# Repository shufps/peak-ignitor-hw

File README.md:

> 🚧 **Work in Progress**  
> This project is under active development.

# 🔥 Peak Ignitor

**Peak Ignitor** is a compact, battery-powered **high-power 12 V supply** designed for one very specific real-world problem:

> *Reliable power in cold, wind, and harsh environments.*

The original trigger was simple:  
lighting a cigarette on a mountain at –10 °C and strong wind — where gas, electric, and plasma lighters all failed.

What *did* work was a classic **car cigarette lighter**:  
wind-proof, temperature-independent, and brutally simple — as long as you can supply enough current.

That requirement immediately defines the problem space:

- 6–10 A at 12 V  
- ~120 W continuous power  
- short but demanding duty cycles  

Peak Ignitor is the result.

---

## What It Is

Peak Ignitor is a **hand-sized, self-contained 12 V power unit** capable of delivering **120 W continuously** (up to ~160 W peak), powered by a **4S Li-Ion battery pack** and designed with **thermal and mechanical constraints as first-class design inputs**.

This is not a power bank and not a jump starter — it sits deliberately in between.

---

## Key Characteristics

- 🔋 **4S Li-Ion Battery System**
  - 4S1P Samsung 18650 (30Q)
  - ~44 Wh energy
  - Proper BMS with balancing and protection
  - Battery operated close to practical limits — intentionally and transparently

- ⚡ **Regulated 12 V Output**
  - High-power buck/boost converter (TI LM51770)
  - ~120 W continuous output
  - ~160 W peak, time-limited
  - Standard automotive cigarette lighter socket

- 🧊 **Mechanics-First Thermal Design**
  - Custom-machined **solid copper heatsink**
  - Direct thermal coupling into the aluminum enclosure
  - The enclosure itself acts as a secondary heatsink
  - Temperature measurement placed directly beneath the heatsink (TMP1075)

- 🧠 **Embedded Control & Monitoring**
  - ESP32-S3 Mini-1
  - Real-time monitoring of voltage, current, power, and temperature
  - Software-enforced safety limits (not just hardware ceilings)
  - Wi-Fi Web UI for observability (because why not 😎)

- 🔌 **Integrated Charging**
  - Onboard Li-Ion charging circuit
  - Balancer connector
  - Fully self-contained — no external hobby charger required

---

## Design Approach

A central idea behind Peak Ignitor is **mechanics-first design**:

The complete 3D model — enclosure, PCB outline, mounting points, heatsink geometry, connector placement, and thermal paths — was created **before** PCB layout and component selection.

This tightly couples:

- Mechanical design  
- PCB layout and form factor  
- Thermal constraints  
- User interaction and front-panel layout  

into a single coherent system.

As a result, the PCB, heatsink, battery pack, and enclosure are not independent parts — they are **co-designed elements of one integrated structure**.

---

## Thermal Philosophy

Thermal management is not an accessory here.

Heat is transferred:
1. from the power electronics  
2. into a custom copper heatsink  
3. directly into the aluminum enclosure  

This effectively turns the entire case into an active thermal component — a design style commonly found in industrial or automotive hardware, but rarely in DIY projects.

Sustained output is **intentionally limited by battery temperature**, not by electronic capability.

---

## Typical Use Cases

- 🔥 **Car cigarette lighter**  
  6–10 A for seconds — trivial load.

- 🏄 **SUP pumps / small compressors**  
  ~110 W continuous at 12 V.

- ⛏️ **NerdQAxe++**  
  ~80 W mobile operation.

- 🔌 **General 12 V loads**  
  Measurement equipment, adapters, field hardware.

---

## What This Project Demonstrates

Peak Ignitor is less about lighting a cigarette — and more about showing what happens when:

- real-world requirements  
- harsh environmental constraints  
- and a refusal to accept “almost good enough”  

meet a **system-level engineering mindset**.

It combines:
- energy storage  
- power electronics  
- thermal engineering  
- mechanical design  
- embedded firmware  

into a compact, honest, high-power device.

---

## Notes

- High-current device — **not a toy**
- Use only suitable loads
- Do not bypass or modify protection mechanisms
- Never operate the battery without the BMS

---

> *A good horse jumps only as high as it needs to.*  
> **Peak Ignitor jumps higher — on purpose.**

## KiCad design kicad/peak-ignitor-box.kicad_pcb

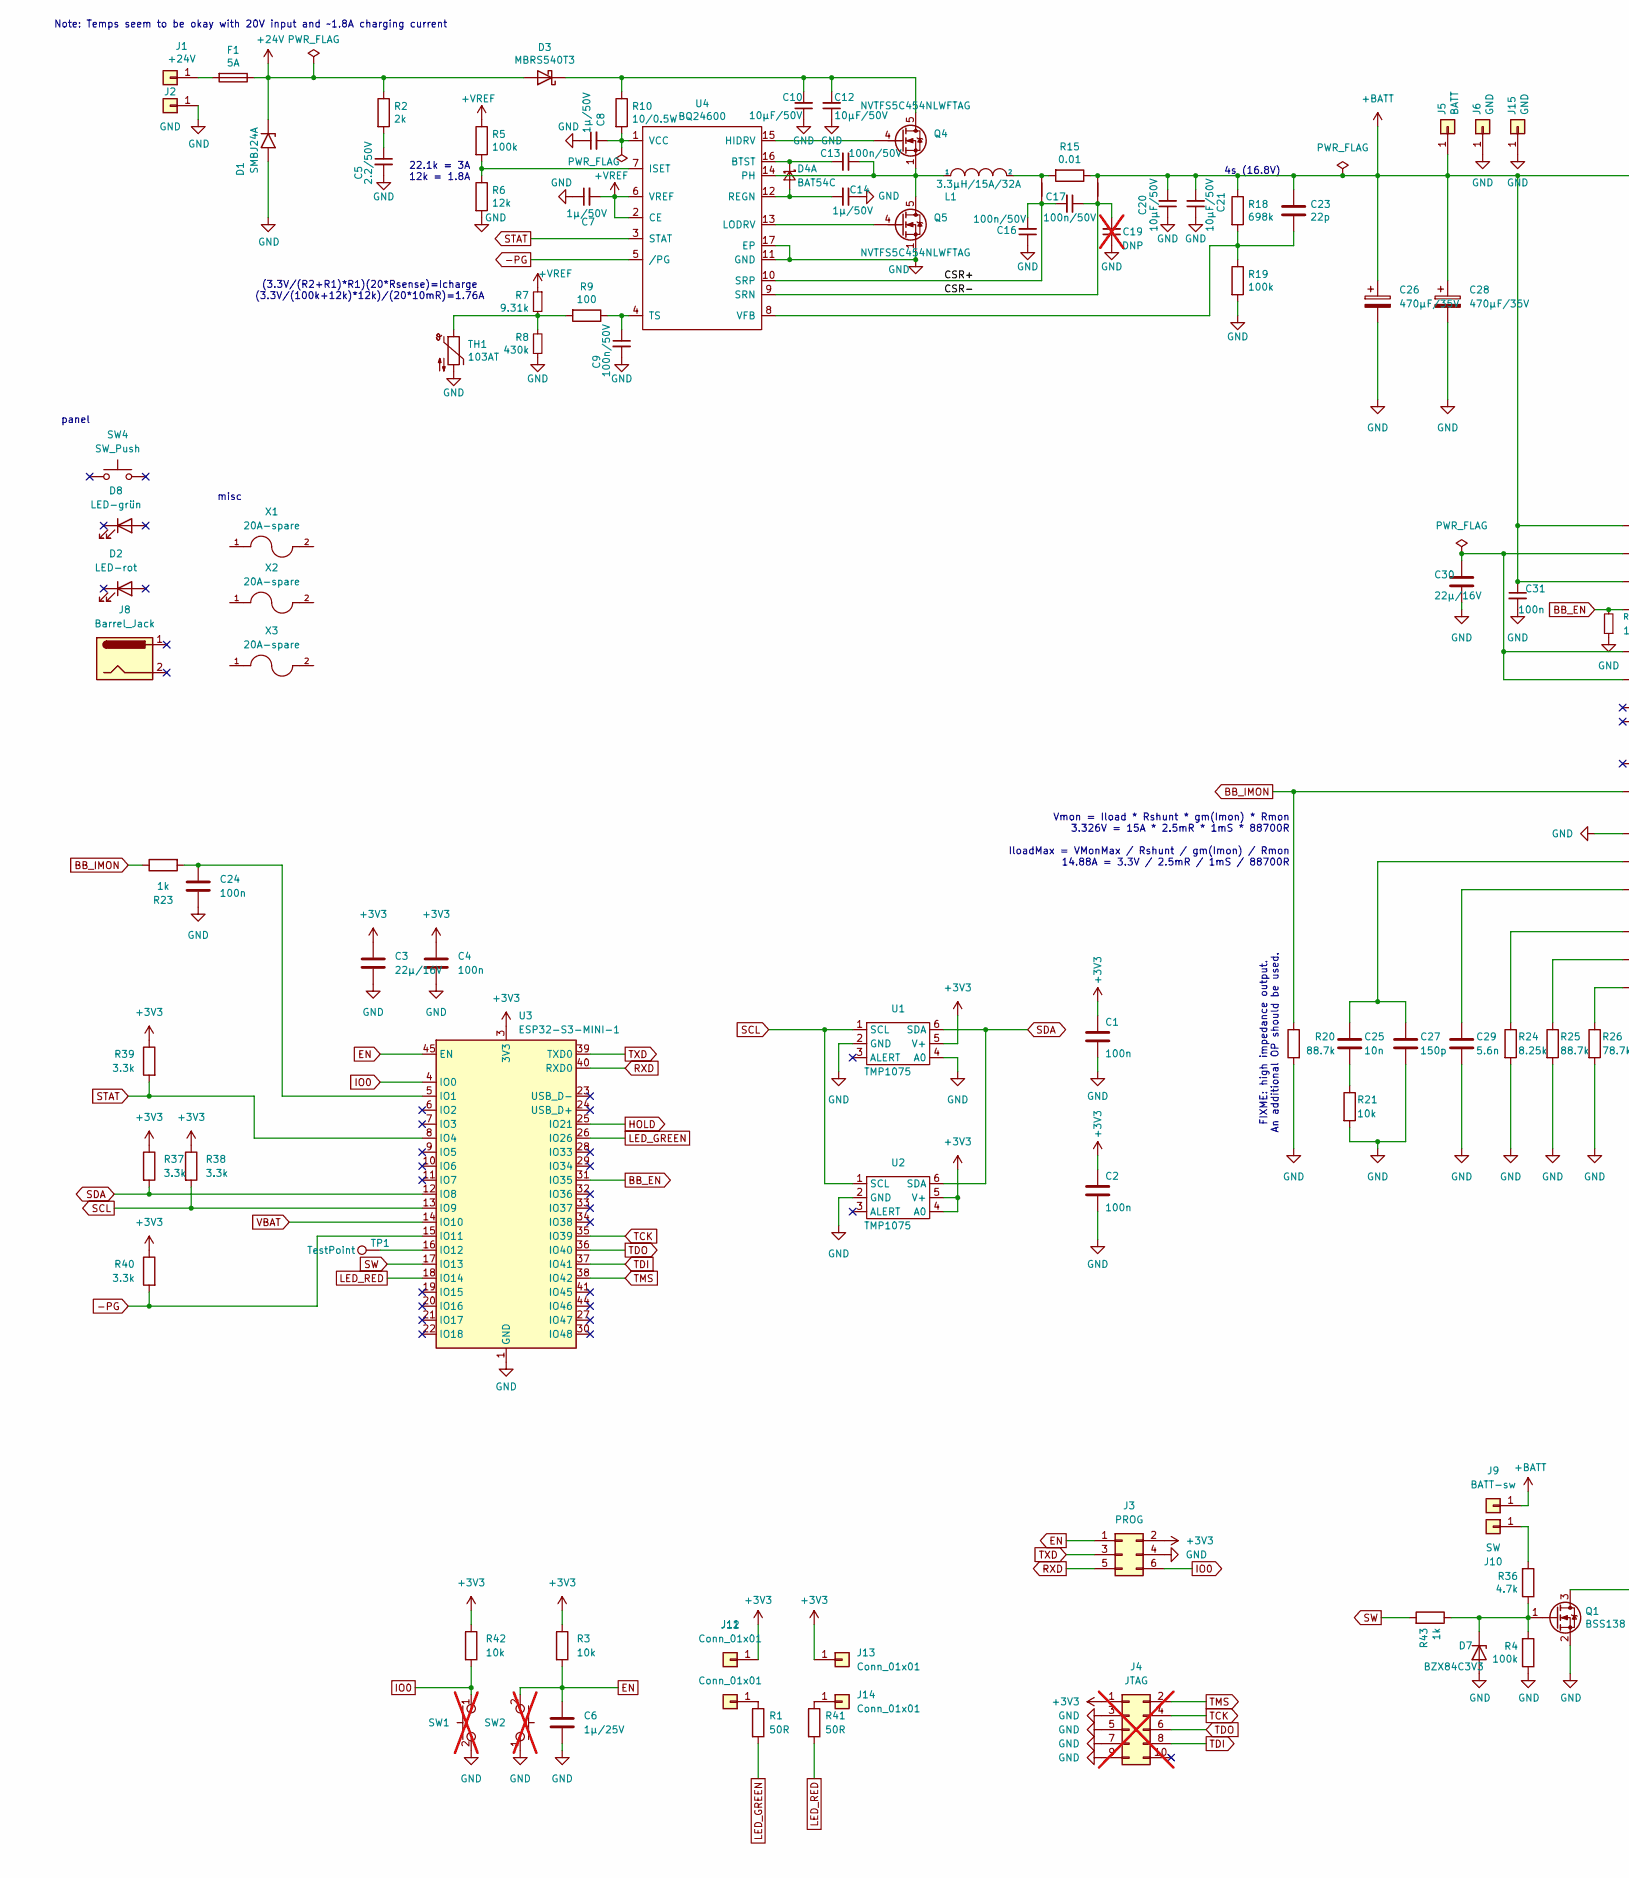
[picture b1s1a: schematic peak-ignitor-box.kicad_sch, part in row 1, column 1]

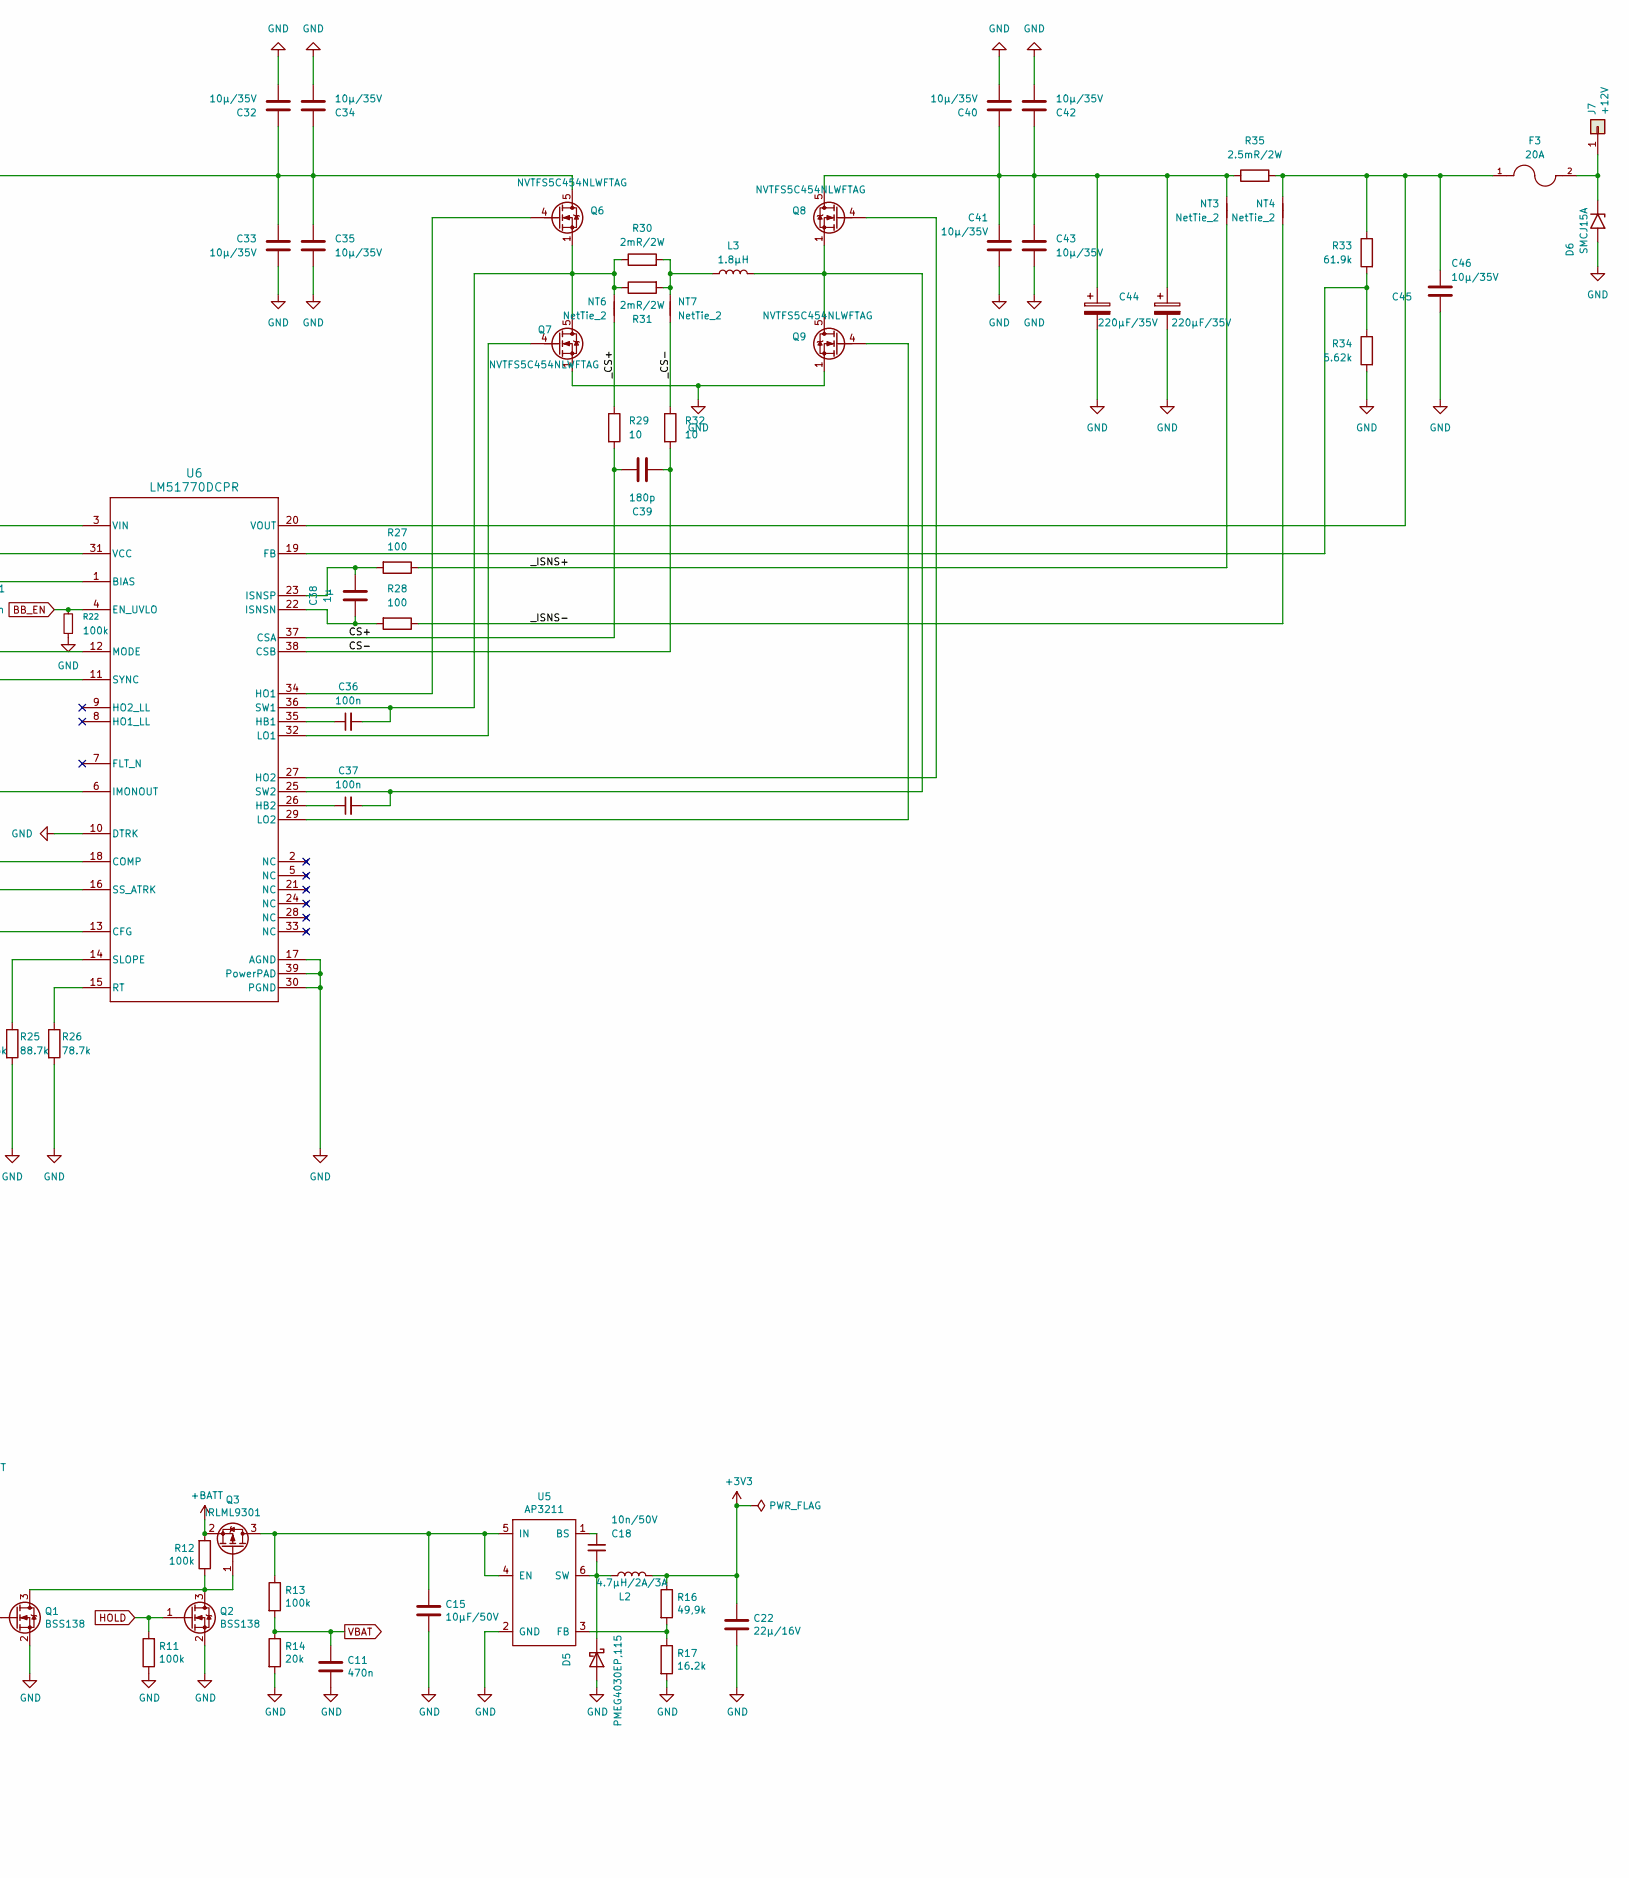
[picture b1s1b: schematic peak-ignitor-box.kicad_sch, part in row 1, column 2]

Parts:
C1, C2, C4, C24, C31, C36, C37: 100n; C_0805_2012Metric
C3, C22, C30: 22µ/16V; C_1206_3216Metric
C5: 2.2/50V; C_1206_3216Metric
C6: 1µ/25V; C_0805_2012Metric; PARTNO EMK105BJ105MV-F
C7, C8, C14: 1µ/50V; C_0805_2012Metric
C9, C13, C16, C17: 100n/50V; C_0805_2012Metric
C10, C12, C15, C20, C21: 10µF/50V; C_1206_3216Metric
C11: 470n; C_0805_2012Metric
C18: 10n/50V; C_0805_2012Metric
C19: DNP; C_0805_2012Metric; not fitted
C23: 22p; C_0603_1608Metric
C25: 10n; C_0805_2012Metric
C26, C28: 470µF/35V; CP_Elec_10x10.5
C27: 150p; C_0603_1608Metric
C29: 5.6n; C_0805_2012Metric
C32, C33, C34, C35, C40, C41, C42, C43, C46: 10µ/35V; C_1210_3225Metric
C38: 1µ; C_0805_2012Metric
C39: 180p; C_0603_1608Metric
C44, C45: 220µF/35V; CP_Elec_10x10.5
D1: SMBJ24A; D_SMB
D2: LED-rot
D3: MBRS540T3; D_SMC
D4: BAT54C; SOT-23
D5: PMEG4030EP,115; D_SOD-128
D6: SMCJ15A; D_SMC
D7: BZX84C3V3; SOT-23
D8: LED-grün
F1: 5A; fuseholder_littlefuse_blok
F3: 20A; Fuseholder_Blade_Mini_Keystone_3568
J1: +24V; TestPoint_Loop_D2.50mm_Drill1.85mm
J2, J6, J15: GND; TestPoint_Loop_D2.50mm_Drill1.85mm
J3: PROG; PinHeader_IDC_2x03_P1.27mm_Vertical_SMD
J4: JTAG; PinHeader_IDC_2x05_P1.27mm_Vertical_SMD; not fitted
J5: BATT; TestPoint_Loop_D2.50mm_Drill1.85mm
J7: +12V; TestPoint_Loop_D2.50mm_Drill1.85mm
J8: Barrel_Jack
J9: BATT-sw; Pin_D1.0mm_L10.0mm
J10: SW; Pin_D1.0mm_L10.0mm
J11, J12, J13, J14: Conn_01x01; Pin_D1.0mm_L10.0mm
L1: 3.3µH/15A/32A; L_Vishay_IHLP-5050
L2: 4.7µH/2A/3A; L_Taiyo-Yuden_NR-50xx
L3: 1.8µH; L_Coilcraft_XAL1580-182
NT1, NT2: Net-Tie_2; NetTie-2_SMD_Pad0.5mm
NT3, NT4, NT6, NT7: NetTie_2; NetTie-2_SMD_Pad0.5mm
Q1, Q2: BSS138; SOT-23
Q3: IRLML9301; SOT-23
Q4, Q5, Q6, Q7, Q8, Q9: NVTFS5C454NLWFTAG; VSON-8_3.3x3.3mm_P0.65mm_NexFET
R1, R41: 50R; R_0805_2012Metric
R2: 2k; R_0805_2012Metric
R3, R21, R42: 10k; R_0805_2012Metric
R4, R5, R11, R12, R13, R19, R22: 100k; R_0805_2012Metric
R6: 12k; R_0805_2012Metric
R7: 9.31k; R_0805_2012Metric
R8: 430k; R_0805_2012Metric
R9, R27, R28: 100; R_0805_2012Metric
R10: 10/0.5W; R_1206_3216Metric
R14: 20k; R_0805_2012Metric
R15: 0.01; R_2010_5025Metric
R16: 49,9k; R_0805_2012Metric
R17: 16.2k; R_0805_2012Metric
R18: 698k; R_0805_2012Metric
R20, R25: 88.7k; R_0805_2012Metric
R23, R43: 1k; R_0805_2012Metric
R24: 8.25k; R_0805_2012Metric
R26: 78.7k; R_0805_2012Metric
R29, R32: 10; R_0805_2012Metric
R30, R31: 2mR/2W; R_2512_6332Metric
R33: 61.9k; R_0805_2012Metric
R34: 5.62k; R_0805_2012Metric
R35: 2.5mR/2W; R_2010_5025Metric
R36: 4.7k; R_0805_2012Metric
R37, R38, R39, R40: 3.3k; R_0805_2012Metric
SW1, SW2: GT-TC029B-H025-L1N; SW_Push_1P1T_NO_CK_KMR2; not fitted
SW4: SW_Push
TH1: 103AT; PinHeader_1x02_P2.54mm_Vertical
TP1: TestPoint; TestPoint_Pad_1.5x1.5mm
U1, U2: TMP1075; TMP1075-DRL
U3: ESP32-S3-MINI-1; ESP32-S2-MINI-1
U4: BQ24600; QFN-16-1EP_3.5x3.5mm_P0.5mm_EP2.14x2.14mm
U5: AP3211; SOT-23-6
U6: LM51770DCPR; DCP0038A-IPC_A
X1, X2, X3: 20A-spare

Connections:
+3V3: C1.1, C2.1, C3.1, C4.1, C22.1, J3.2, J4.1, J11.1, J13.1, L2.2, R3.1, R16.1, R37.1, R38.1, R39.1, R40.1, R42.1, U1.5 (V+), U2.4 (A0), U2.5 (V+), U3.3 (3V3)
+24V: D1.1 (A1), D3.2 (A), F1.1, R2.1
+BATT: C20.2, C21.2, C23.1, C26.1, C28.1, C31.1, C32.1, C33.1, C34.1, C35.1, J5.1, J9.1, NT2.2, Q3.2 (S), Q6.5 (D), R12.2, R15.1, R18.1, U6.1 (BIAS), U6.3 (VIN)
+VREF: C7.2, R5.1, R7.1, U4.2 (CE), U4.6 (VREF)
-PG: R40.2, U3.15 (IO11), U4.5 (/PG)
/CS+: C39.2, R29.2, U6.37 (CSA)
/CS-: C39.1, R32.2, U6.38 (CSB)
/CSR+: C16.2, C17.2, NT1.1, U4.10 (SRP)
/CSR-: C17.1, C19.2, NT2.1, U4.9 (SRN)
/_CS+: NT6.1, R29.1
/_CS-: NT7.1, R32.1
/_ISNS+: NT3.1, R27.1
/_ISNS-: NT4.1, R28.1
BB_EN: R22.2, U3.31 (IO35), U6.4 (EN_UVLO)
BB_IMON: R20.1, R23.1, U6.6 (IMONOUT)
EN: C6.1, J3.1, R3.2, SW2.2, U3.45 (EN)
GND: C1.2, C2.2, C3.2, C4.2, C5.2, C6.2, C7.1, C8.1, C9.2, C10.1, C11.2, C12.1, C14.1, C15.2, C16.1, C19.1, C20.1, C21.1, C22.2, C24.2, C26.2, C27.2, C28.2, C29.2, C30.2, C31.2, C32.2, C33.2, C34.2, C35.2, C40.2, C41.2, C42.2, C43.2, C44.2, C45.2, C46.2, D1.2 (A2), D5.2 (A), D6.2 (A2), D7.1 (A), J2.1, J3.4, J4.3, J4.5, J4.7, J4.9, J6.1, J15.1, Q1.2 (S), Q2.2 (S), Q5.1 (S), Q5.2 (S), Q5.3 (S), Q7.1 (S), Q7.2 (S), Q7.3 (S), Q9.1 (S), Q9.2 (S), Q9.3 (S), R4.1, R6.2, R8.1, R11.1, R14.2, R17.2, R19.2, R20.2, R21.2, R22.1, R24.2, R25.2, R26.2, R34.2, SW1.2, SW2.1, TH1.2, U1.2 (GND), U1.4 (A0), U2.2 (GND), U3.1 (GND), U3.2 (GND), U3.42 (GND), U3.43 (GND), U3.46 (GND), U3.47 (GND), U3.48 (GND), U3.49 (GND), U3.50 (GND), U3.51 (GND), U3.52 (GND), U3.53 (GND), U3.54 (GND), U3.55 (GND), U3.56 (GND), U3.57 (GND), U3.58 (GND), U3.59 (GND), U3.60 (GND), U3.61 (GND), U3.62 (GND), U3.63 (GND), U3.64 (GND), U3.65 (GND), U4.11 (GND), U4.17 (EP), U5.2 (GND), U6.10 (DTRK), U6.17 (AGND), U6.30 (PGND), U6.39 (PowerPAD)
HOLD: Q2.1 (G), R11.2, U3.25 (IO21)
IO0: J3.6, R42.2, SW1.1, U3.4 (IO0)
LED_GREEN: R1.2, U3.26 (IO26)
LED_RED: R41.2, U3.18 (IO14)
unnamed: C5.1, R2.2
unnamed: C25.2, R21.1
unnamed: C10.2, C12.2, D3.1 (K), Q4.5 (D), R10.1
unnamed: C14.2, D4.1 (A), U4.12 (REGN)
unnamed: C13.2, D4.3 (K), U4.16 (BTST)
unnamed: C18.2, D5.1 (K), L2.1, U5.6 (SW)
unnamed: D6.1 (A1), F3.2, J7.1
unnamed: D7.3 (K), Q1.1 (G), R4.2, R36.1, R43.1
unnamed: F1.2, J1.1
unnamed: J10.1, R36.2
unnamed: J12.1, R1.1
unnamed: J14.1, R41.1
unnamed: L1.2, NT1.2, R15.2
unnamed: L3.1, NT7.2, R30.2, R31.2
unnamed: Q1.3 (D), Q2.3 (D), Q3.1 (G), R12.1
unnamed: C15.1, Q3.3 (D), R13.1, U5.4 (EN), U5.5 (IN)
unnamed: Q4.4 (G), U4.15 (HIDRV)
unnamed: C13.1, L1.1, Q4.1 (S), Q4.2 (S), Q4.3 (S), Q5.5 (D), U4.14 (PH)
unnamed: Q5.4 (G), U4.13 (LODRV)
unnamed: Q6.4 (G), U6.34 (HO1)
unnamed: C36.2, NT6.2, Q6.1 (S), Q6.2 (S), Q6.3 (S), Q7.5 (D), R30.1, R31.1, U6.36 (SW1)
unnamed: Q7.4 (G), U6.32 (LO1)
unnamed: C40.1, C41.1, C42.1, C43.1, C44.1, C45.1, NT3.2, Q8.5 (D), R35.1
unnamed: Q8.4 (G), U6.27 (HO2)
unnamed: C37.2, L3.2, Q8.1 (S), Q8.2 (S), Q8.3 (S), Q9.5 (D), U6.25 (SW2)
unnamed: Q9.4 (G), U6.29 (LO2)
unnamed: R7.2, R8.2, R9.2, TH1.1
unnamed: C24.1, R23.2, U3.5 (IO1)
unnamed: TP1.1, U3.16 (IO12)
unnamed: R5.2, R6.1, U4.7 (ISET)
unnamed: C9.1, R9.1, U4.4 (TS)
unnamed: C8.2, R10.2, U4.1 (VCC)
unnamed: C23.2, R18.2, R19.1, U4.8 (VFB)
unnamed: C18.1, U5.1 (BS)
unnamed: R16.2, R17.1, U5.3 (FB)
unnamed: R24.1, U6.13 (CFG)
unnamed: C25.1, C27.1, U6.18 (COMP)
unnamed: R33.2, R34.1, U6.19 (FB)
unnamed: C36.1, U6.35 (HB1)
unnamed: C37.1, U6.26 (HB2)
unnamed: C38.1, R28.2, U6.22 (ISNSN)
unnamed: C38.2, R27.2, U6.23 (ISNSP)
unnamed: C30.1, U6.11 (SYNC), U6.12 (MODE), U6.31 (VCC)
unnamed: R26.1, U6.15 (RT)
unnamed: R25.1, U6.14 (SLOPE)
unnamed: C29.1, U6.16 (SS_ATRK)
unnamed: C46.1, F3.1, NT4.2, R33.1, R35.2, U6.20 (VOUT)
RXD: J3.5, U3.40 (RXD0)
SCL: R38.2, U1.1 (SCL), U2.1 (SCL), U3.13 (IO9)
SDA: R37.2, U1.6 (SDA), U2.6 (SDA), U3.12 (IO8)
STAT: R39.2, U3.8 (IO4), U4.3 (STAT)
SW: R43.2, U3.17 (IO13)
TCK: J4.4, U3.35 (IO39)
TDI: J4.8, U3.37 (IO41)
TDO: J4.6, U3.36 (IO40)
TMS: J4.2, U3.38 (IO42)
TXD: J3.3, U3.39 (TXD0)
VBAT: C11.1, R13.2, R14.1, U3.14 (IO10)

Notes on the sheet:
Note: Temps seem to be okay with 20V input and ~1.8A charging current
(3.3V/(R2+R1)*R1)(20*Rsense)=Icharge (3.3V/(100k+12k)*12k)/(20*10mR)=1.76A
Vmon = Iload * Rshunt * gm(Imon) * Rmon 3.326V = 15A * 2.5mR * 1mS * 88700R IloadMax = VMonMax / Rshunt / gm(Imon) / Rmon 14.88A = 3.3V / 2.5mR / 1mS / 88700R
panel
FIXME: high impedance output. An additional OP should be used.
misc
22.1k = 3A 12k = 1.8A
4s (16.8V)

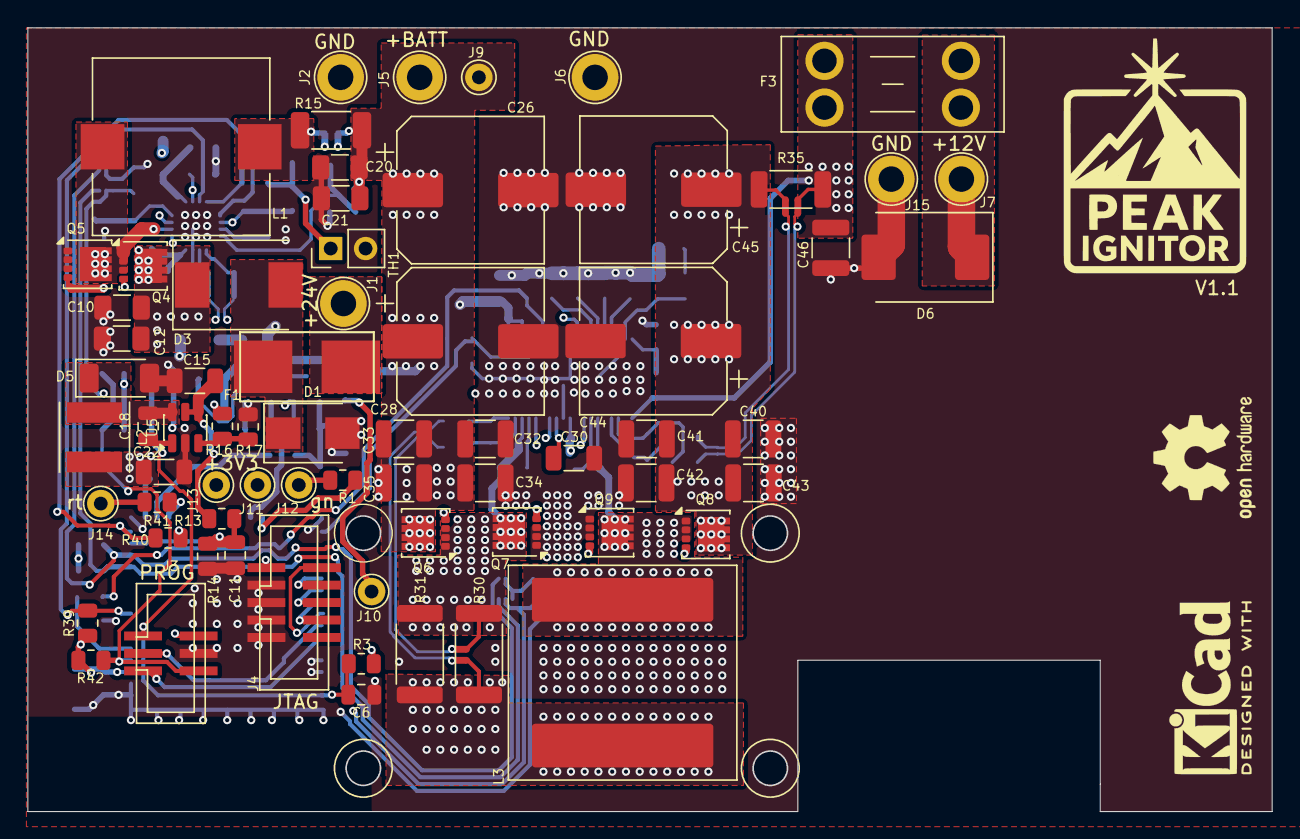
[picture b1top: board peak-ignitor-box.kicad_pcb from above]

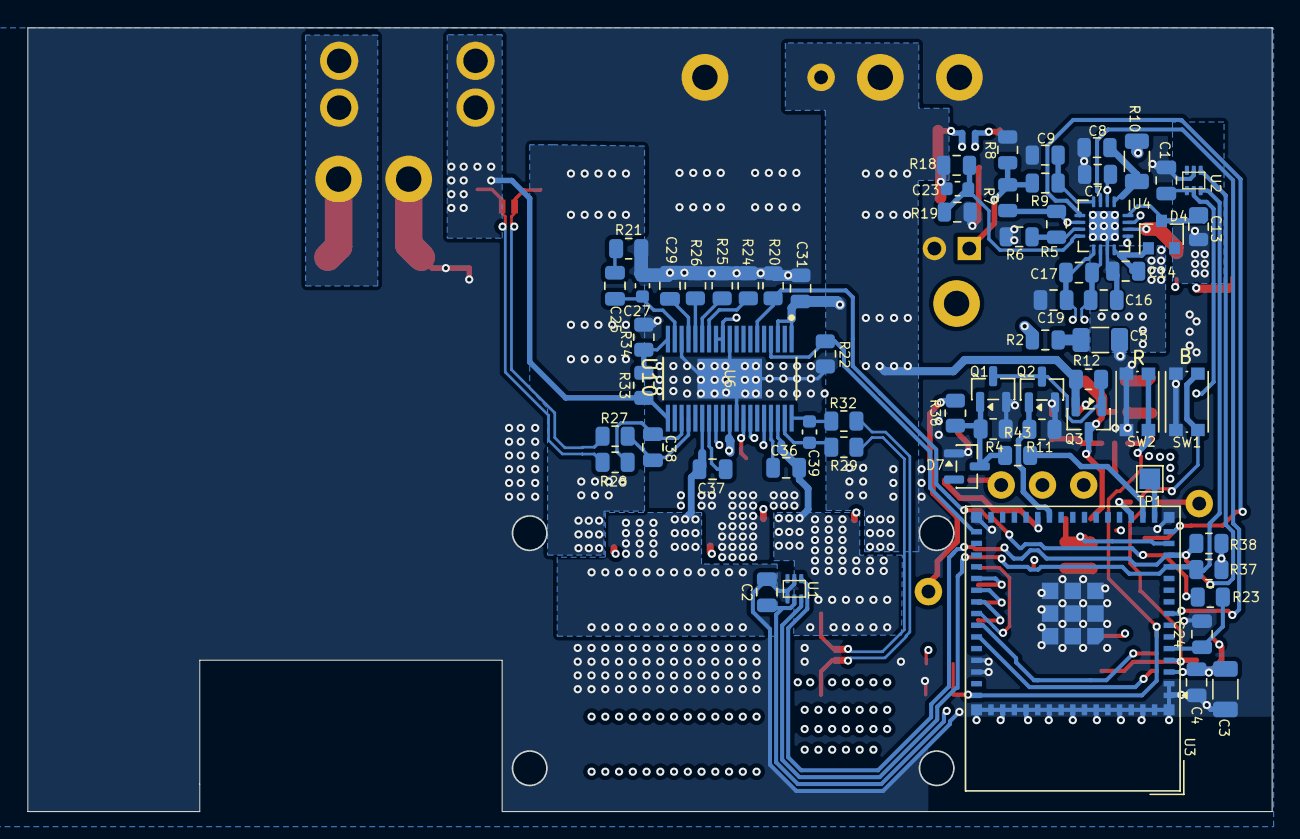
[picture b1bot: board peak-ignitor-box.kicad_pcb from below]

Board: 4 copper layers, 90.5 x 57.0 mm, 139 parts (67 on the bottom side), 79 nets.

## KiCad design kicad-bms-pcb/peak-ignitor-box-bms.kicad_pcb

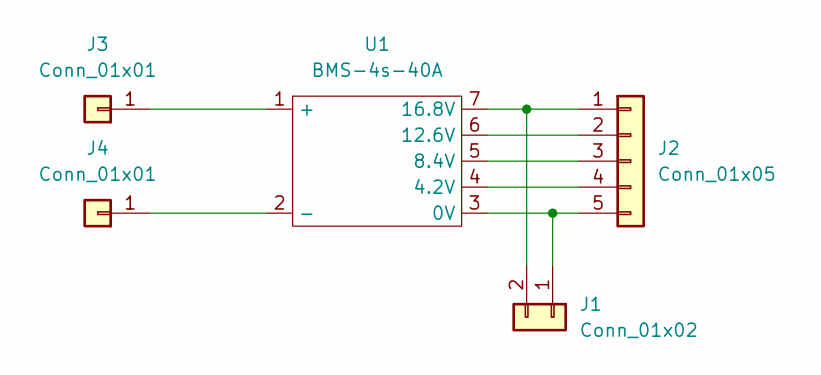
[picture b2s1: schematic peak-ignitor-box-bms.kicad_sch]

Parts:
J1: Conn_01x02; AMASS_XT30PW-M_1x02_P2.50mm_Horizontal
J2: Conn_01x05; JST_XH_S5B-XH-A-1_1x05_P2.50mm_Horizontal
J3, J4: Conn_01x01; MountingHole_4.3mm_M4_DIN965_Pad
U1: BMS-4s-40A; bms-4s-40A

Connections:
unnamed: J1.1, J2.5, U1.3 (0V)
unnamed: J1.2, J2.1, U1.7 (16.8V)
unnamed: J2.2, U1.6 (12.6V)
unnamed: J2.3, U1.5 (8.4V)
unnamed: J2.4, U1.4 (4.2V)
unnamed: J3.1, U1.1 (+)
unnamed: J4.1, U1.2 (-)

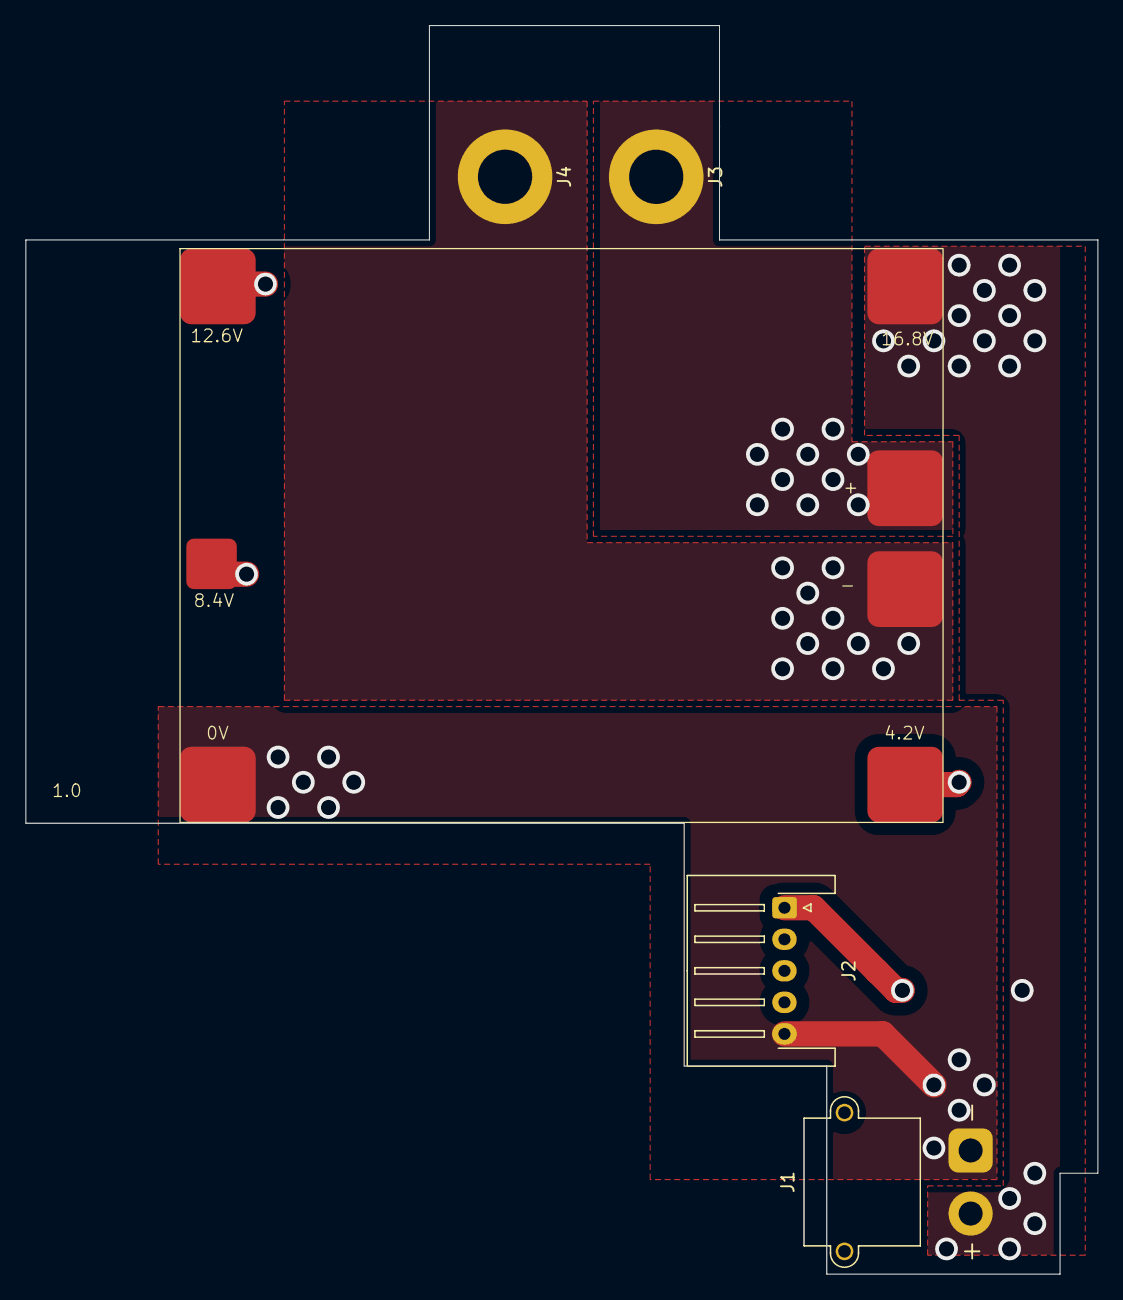
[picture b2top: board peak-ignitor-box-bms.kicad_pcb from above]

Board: 4 copper layers, 85.0 x 99.0 mm, 5 parts (0 on the bottom side), 7 nets.

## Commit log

2025-12-20 added all case files
2025-12-20 added gerbers
2025-12-20 moved a bit
2025-12-20 added 3d rendering
2025-12-20 added li-ion battery
2025-12-20 bom for bms pcb
2025-12-20 AI summary
2025-12-20 Update description of Peak Ignitor features
2025-12-21 added lm51770 step
2025-12-26 updated gerbers, bom, some bug fixes on schematic and board
2025-12-27 Update power specifications in README
2025-12-27 added pictures
2025-12-27 added plots for charge and 120W discharge
2025-12-29 added 160W discharge
2026-01-01 rev1.1
2026-01-02 push
2026-01-02 images
2026-01-02 updated gerbers, bom, ibom
2026-01-02 Update README with status badge and WIP notice
    Added status badge and work in progress note to README.
2026-01-05 updated bms carrier
